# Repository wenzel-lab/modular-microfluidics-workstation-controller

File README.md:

# "Rio controller" the modular microfluidics controller 

This repository contains the free and *open-source* design and documentation for the *brain of a microfluidics workstation* to enable *high-throughput droplet microfluidic* biological assays. The design contains an electronics board "hat" that plugs onto a Raspberry Pi single-board computer and interfaces with our *compact* *modules* e.g. for gas-pressure control to push microfluidic samples onto chips, pressure, and flow measurement with feedback control, sample holders with heating and stirring, and imaging of fast droplet generation processes with open-source microscopy and stroboscopic illumination

Our aim is to create a prototype of a *compact* working station that is based on *connectable*, *open*, modern, and *low-cost* components (Rasberry Pi, Arduino, 3D printing, on-board components, open or at least accessible design software and operation software - python). This workstation is aimed to be fully functional research-grade equipment with good specifications, such as fast reaction times and low-pressure fluctuations. It is modular so that parts of the workstation can be repurposed and improved in the open-source hardware sense and easily combined, exchanged, or used independently in challenging environments such as an anaerobic chamber.

This is an open, collaborative project by the Wenzel Lab in Chile, and *your participation* (comments, inputs, contributions) are explicitly welcome! Please submit your message as an issue in this repository to participate.

> **Please Note:** This technical index is very much under construction and is at present an incomplete summary of the various documents that exist elsewhere in the Open Microfluidics Workstation repositories on GitHub and elsewhere.

Follow us! [#twitter](https://twitter.com/WenzelLab), [#YouTube](https://www.youtube.com/@librehub), [#LinkedIn](https://www.linkedin.com/company/92802424), [#instagram](https://www.instagram.com/wenzellab/), [#Printables](https://www.printables.com/@WenzelLab), [#LIBREhub website](https://librehub.github.io), [#IIBM website](https://ingenieriabiologicaymedica.uc.cl/en/people/faculty/821-tobias-wenzel)

<!--- ## Table of Contents --->

<!--- ## Background --->

## Usage

* Installation instructions
    * [Software installation](https://github.com/wenzel-lab/moldular-microfluidics-workstation-controller/wiki/Install-the-Software)
* Our modules are used in our [flow-microscopy-platform, see repostiory for documentation and instructions](https://github.com/wenzel-lab/flow-microscopy-platform)
* And it also powers our [strobe-enhanced microscopy stage](https://wenzel-lab.github.io/strobe-enhanced-microscopy-stage/) see also [it's repository](https://github.com/wenzel-lab/strobe-enhanced-microscopy-stage) 

## Design files and source code

* Hardware designs
    * [Fast imaging module](https://github.com/wenzel-lab/moldular-microfluidics-workstation-controller/tree/master/module-fast-imaging)
    * [Pressure and flow controller module](https://github.com/wenzel-lab/moldular-microfluidics-workstation-controller/tree/master/module-pressure-and-flow-controller)
    * [Sample holders module](https://github.com/wenzel-lab/moldular-microfluidics-workstation-controller/tree/master/module-sample-holders)
 
* Software source code
    * [Microfluidics workstation server](https://github.com/wenzel-lab/moldular-microfluidics-workstation-controller/blob/master/module-pi/webapp.zip) (This code runs on the built-in Raspberry Pi and includes the web application for the user interface.

### Modules Wish List
* High-pressure source module to replace large gas bottles with a small soda CO2 bottle, developed in this [sub-repository](https://github.com/wenzel-lab/moldular-microfluidics-workstation-controller/tree/master/module-high-pressure-source)
* Support for small piezo pumps
* Smart cultivation sleeves for vials, smaller and with OD-tracking - the V2 of our current sample holders and strirrers
* Microfluidic droplet sorting workstation driven by the droplet workstation tools is described [here](https://github.com/wenzel-lab/droplet-sorter-master/tree/main) (This is being developed in a separate repository).
  
## Contribute

Feel free to dive in! [Open an issue](https://github.com/wenzel-lab/moldular-microfluidics-workstation-controller/issues/new).
For interactions in our team and with the community applies the [GOSH Code of Conduct](https://openhardware.science/gosh-2017/gosh-code-of-conduct/).

## License

[CERN OHL 2W](LICENSE) © Tobias Wenzel, Christie Nel, and Pierre Padilla-Huamantinco. This project is Open-Source Hardware - please acknowledge us when using the hardware or sharing modifications.

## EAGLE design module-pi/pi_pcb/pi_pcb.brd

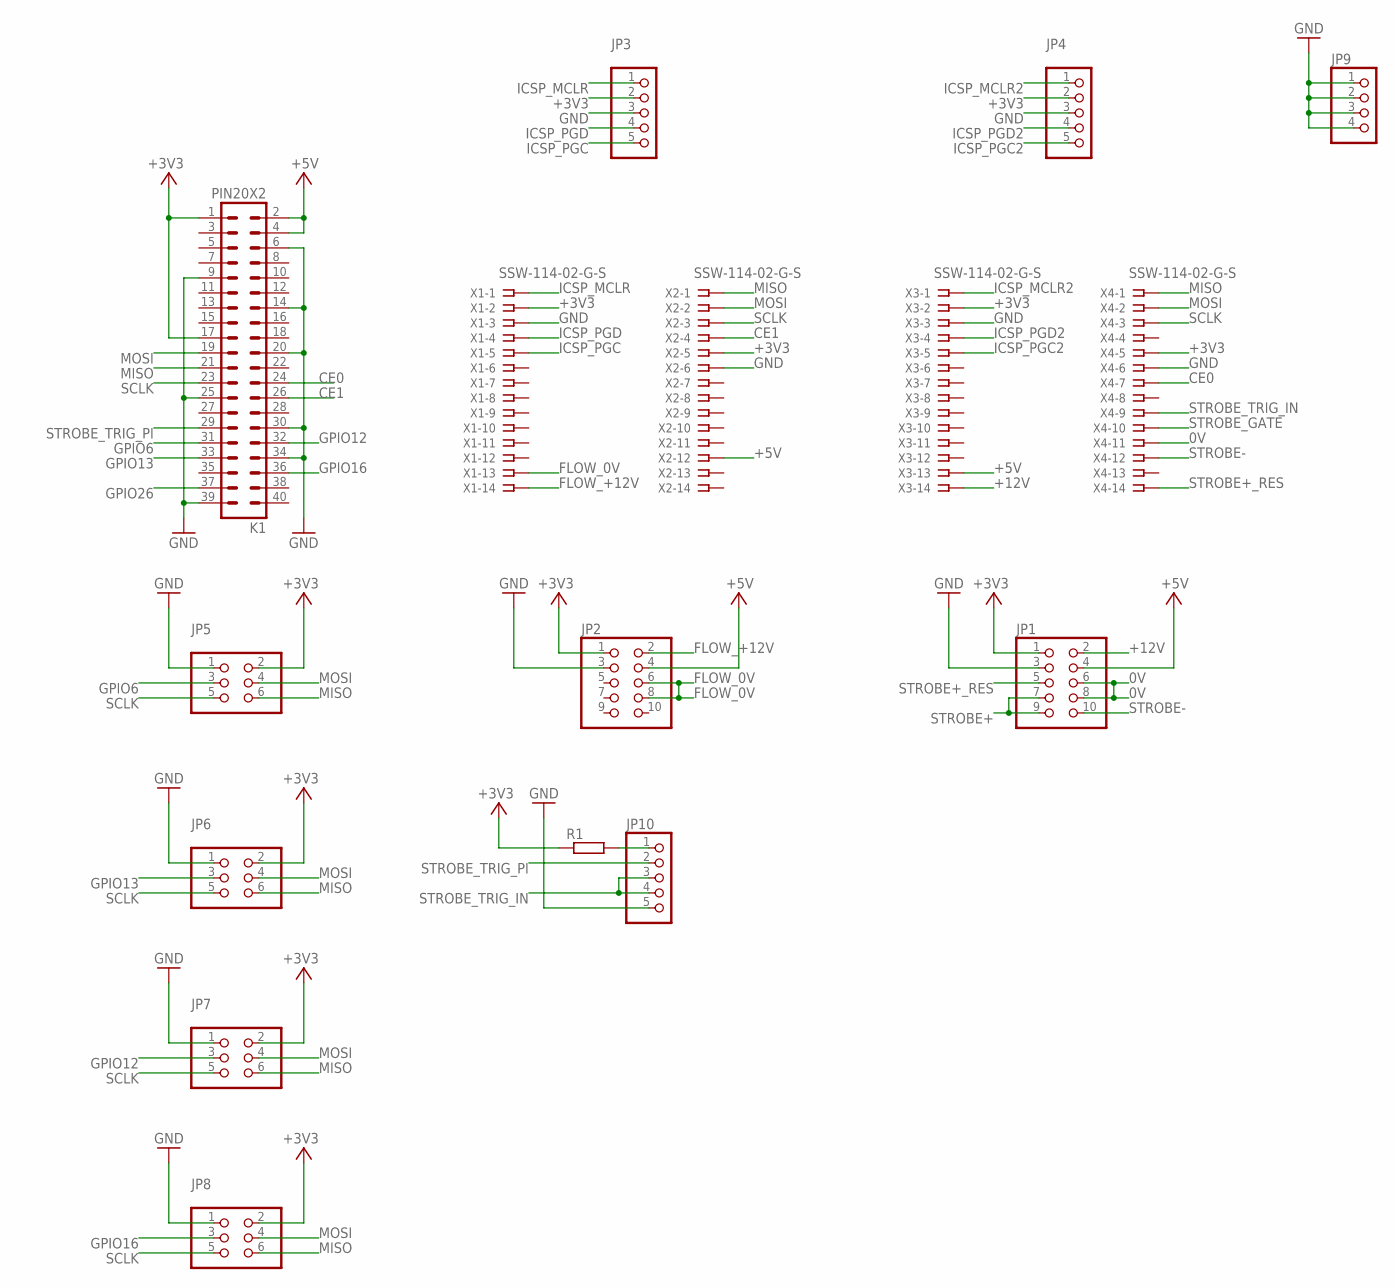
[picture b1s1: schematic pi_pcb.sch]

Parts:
JP1, JP2: PINHD-2X5; 2X05
JP3, JP4, JP10: PINHD-1X5; 1X05
JP5, JP6, JP7, JP8: PINHD-2X3; 2X03
JP9: PINHD-1X4; 1X04
K1: PIN20X2; PIN_20X2
R1: R-EU_R1206; R1206
X1, X2, X3, X4: SSW-114-02-G-S

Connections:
0V: JP1.6, JP1.8, X4.11
+3V3: JP1.1, JP2.1, JP3.2, JP4.2, JP5.2, JP6.2, JP7.2, JP8.2, K1.1, K1.17, R1.1, X1.2, X2.5, X3.2, X4.5
+5V: JP1.4, JP2.4, K1.2, K1.4, X2.12, X3.13
+12V: JP1.2, X3.14
CE0: K1.24, X4.7
CE1: K1.26, X2.4
FLOW_0V: JP2.6, JP2.8, X1.13
FLOW_+12V: JP2.2, X1.14
GND: JP1.3, JP2.3, JP3.3, JP4.3, JP5.1, JP6.1, JP7.1, JP8.1, JP9.1, JP9.2, JP9.3, JP9.4, JP10.5, K1.6, K1.9, K1.14, K1.20, K1.25, K1.30, K1.34, K1.39, X1.3, X2.6, X3.3, X4.6
GPIO6: JP5.3, K1.31
GPIO12: JP7.3, K1.32
GPIO13: JP6.3, K1.33
GPIO16: JP8.3, K1.36
GPIO26: K1.37
ICSP_MCLR: JP3.1, X1.1
ICSP_MCLR2: JP4.1, X3.1
ICSP_PGC: JP3.5, X1.5
ICSP_PGC2: JP4.5, X3.5
ICSP_PGD: JP3.4, X1.4
ICSP_PGD2: JP4.4, X3.4
MISO: JP5.6, JP6.6, JP7.6, JP8.6, K1.21, X2.1, X4.1
MOSI: JP5.4, JP6.4, JP7.4, JP8.4, K1.19, X2.2, X4.2
unnamed: JP10.1, R1.2
SCLK: JP5.5, JP6.5, JP7.5, JP8.5, K1.23, X2.3, X4.3
STROBE+: JP1.7, JP1.9
STROBE+_RES: JP1.5, X4.14
STROBE-: JP1.10, X4.12
STROBE_GATE: X4.10
STROBE_TRIG_IN: JP10.3, JP10.4, X4.9
STROBE_TRIG_PI: JP10.2, K1.29

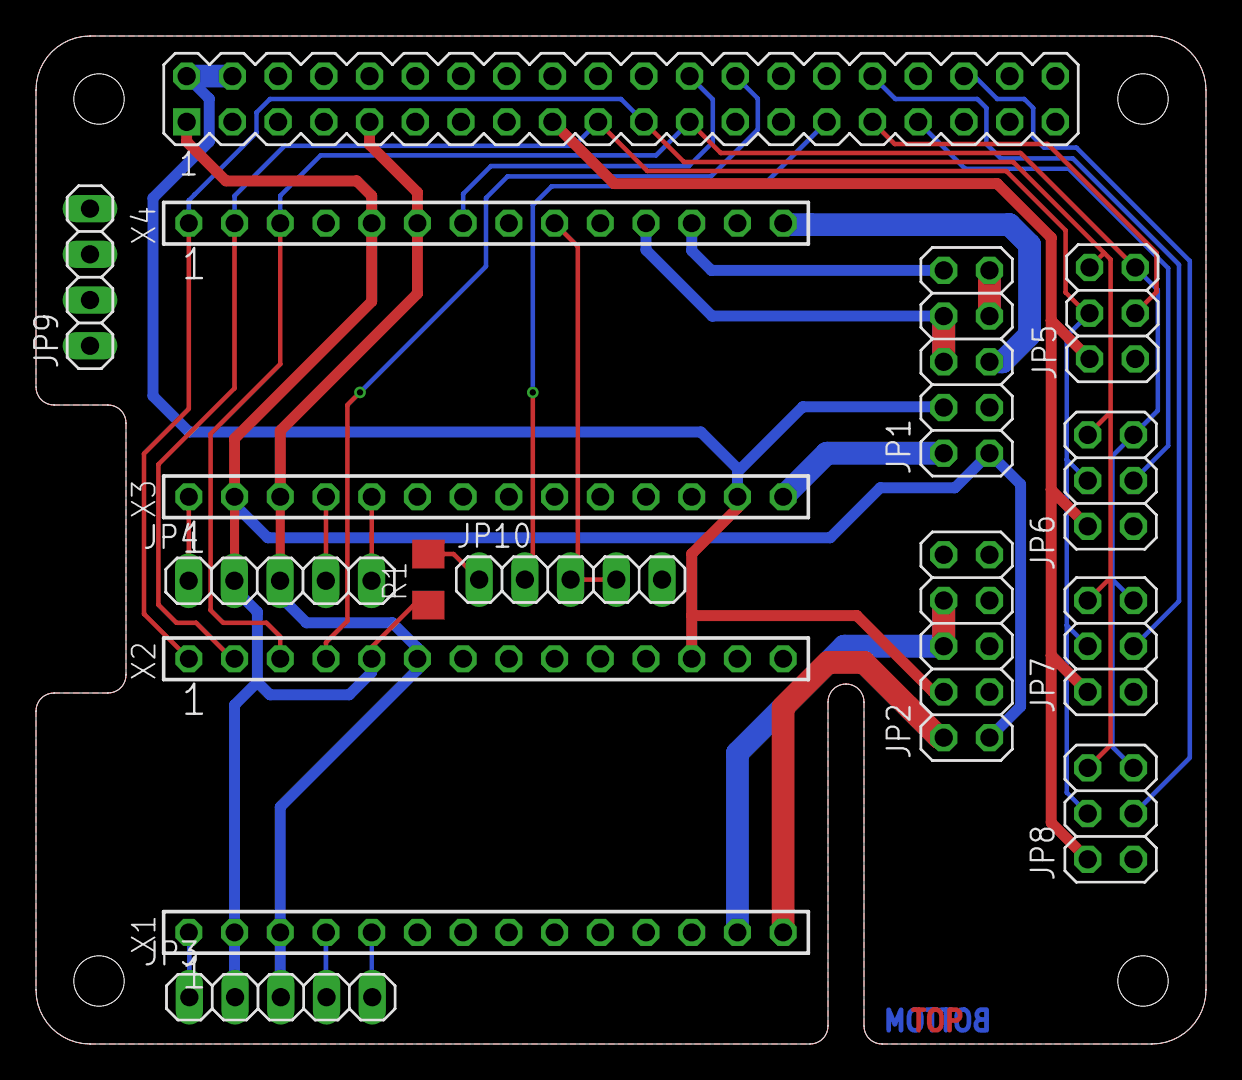
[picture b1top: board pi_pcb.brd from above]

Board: 2 copper layers, 65.0 x 56.0 mm, 16 parts (0 on the bottom side), 28 nets.

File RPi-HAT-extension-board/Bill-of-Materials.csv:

Item #,Ref Des,Full Name/Description,Category,Part/Catalog Number,Manufacturer/Supplier,Notes
,R1,RES SMD 1K OHM 1% 1/4W 1206,HAT,MCR18EZPF1001,Rohm Semiconductor,https://www.digikey.com/en/products/detail/rohm-semiconducto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
,"JP1, JP2","Header - 2x5 Pin (Male, 1.27mm)",HAT,PRT-15362,,https://www.sparkfun.com/header-2x5-pin-male-1-27mm.html
,"JP3, JP4, JP10",Header - 1x5 Pin,HAT,,,
,"JP5, JP6, JP7, JP8","Header - 2x3 (Male, 0.1"")",HAT,PRT-12807,,https://www.sparkfun.com/header-2x3-male-0-1.html
,JP9,Header - 1x4 Pin,HAT,,,
,K1,"Female Header: 2x20-Pin, Straight",HAT,,,https://www.pololu.com/product/1037
,"X1, X2, X3, X4","14-Contact, 1-Row, 2.54mm Pitch, Solder Termination",HAT,,,https://uk.rs-online.com/web/p/pcb-sockets/7655770

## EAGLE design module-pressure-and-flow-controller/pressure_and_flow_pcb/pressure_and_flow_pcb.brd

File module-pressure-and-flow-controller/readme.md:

## Pressure and flow controller module

This is the core piece of the workstation. 
This electronic controller module aims to regulate and distrbute the pressure (originating from the pressure source module) into the sample tubes, so that the samples (aqueous, gel pre-cursors and oils) flow onto the microfluidic chip and the collection reservoirs.
We aim to regulate pressures enough for ultra-high throughput agarose bead generation (several bar), in a smooth fashion that avoids pulsing, especially at steady state.
This controller consists of a custom circuit board that plugs into the Raspberry Pi hat, in addition to connectors for connecting external pressure controllers and flow sensors. Pressure and flow control are fully automatic.

The controller module can operate either in pressure control mode or flow control mode.  Flow control mode requires external flow sensors to be connected.  Once desired flow rates have been achieved and associated pressures are known, the experiment can be reproduced using only pressure control, without the need for expensive flow sensors.  Both modes require external pressure controllers to be connected.

The module contains a PIC microcontroller that communicates with the Raspberry Pi, controls the pressure controllers and reads back pressure and flow.  The pressure target is controlled using a digital-to-analogue converter and the actual pressure is read using an analogue-to-digital converter.  The flow controllers is read via a four channel I2C multiplexer.

### Pressure Controllers
We have selected the SMC ITV0010 pressure controllers for this application.  The pressure target is supplied to the pressure controller by the module as an analogue voltage and the measured pressure achieved is returned as an analogue voltage.  This approach allows the option to connect alternative analogue pressure controllers, or using a separate pressure sensor instead of the one internal to the pressure controller.

The ITV0010 pressure controllers can be purchased as a compact DIN-mounted manifold block that requires a single pressure supply line.

### Flow Sensors
We have selected the Sensirion LG16 range of flow sensor.  They feature a digital interface via I2C.

### Connectors

The module features eight Picoblade connectors.  Four connect to the pressure controllers, carrying power, analogue out and analogue in.  The other four connect to the optional flow sensors and carry power and I2C signals.  The module itself is designed to plug into the Raspberry Pi hat.  This allows for power and digital communications with the Raspberry Pi.

#### Pressure Controller Connector

|Pin|Description|
|-|-|
|1|Pressure In|
|2|Pressure Out|
|3|0V Power / GND|
|4|12V Power|

#### Flow Sensor Connector

|Pin|Description|
|-|-|
|1|I2C Data|
|2|Vdd 3.3V|
|3|Vss (Digital Ground)|
|4|I2C Clock|

**Note:** Pin 2 (Vdd 3.3V) must not be used to power Sensirion LG16 sensors, which require 5V.  This 3.3V pin was intended for use with the Sensirion SLF3S-1300F.  Instead use the 5V pin on the Controller Module header block on the Raspberry Pi hat.

### Pinout

|Pin|Description|
|-|-|
|1|ICSP MCLR|
|2|ICSP Vdd (3V3 Power)|
|3|ICSP Vss (Digital Ground)|
|4|ICSP Data|
|5|ICSP Clock|
|13|Ground for 12V|
|14|12V Supply for Pressure Controllers|
|17|5V Digital Power|
|23|Digital Ground|
|24|Digital 3.3V Power|
|25|SPI Slave Select|
|26|SPI Clock|
|27|SPI MOSI|
|28|SPI MISO|

**Note:** Pin 13 (12V Ground) must be connected with pin 23 (digital ground) externally, and in a way that prevents ground loops.

### PCB Components

|Qty|Name|Component|Description|
|-|-|-|-|
|7|C1-C5,C8-C9|100nf Capacitor 0603|Decoupling Capacitors|
|2|C6,C10|10uF Capacitor 0603|Bypass,Bulk Capacitor|
|1|C7|Not fitted||
|1|C2|dsPIC33CK256MP502-I/SS SSOP28|PIC Microprocessor|
|1|C3|AD5624R|DAC|
|1|C4|ADS1115|ADC|
|1|C5|PCA9544APW,112|I2C Multiplexer|
|1|C6|25AA040ST|EEPROM|
|12|R1-R10,R12-R13|1k Resistor 0603||
|1|R11|10k Resistor 0603||
|8|X1-X8|Picoblade 53047-0410|Connectors|

Please note that our current implementation is based on compact, low-cost and scalable PIC microcontrollers that fit onto the Pi-hat modules. These cannot simply be programmed with a micro-USB cables. Instead, they need an [additional small hardware ICSP interface](https://www.digikey.com/en/product-highlight/m/microchip-technology/pickit-3-in-circuit-debugger-programmer) (or equivalent) to load new code onto the PIC microcontrollers.

### Cable for Sensirion LG16

Flow Controller Module End

Connector Type: Picoblade 1.25mm 4-way (51021-0400)<br/>
Connector Crimps: Picoblade 26-28 AWG (50079-8000)

|Pin|Wire|Function|
|-|-|-|
|1|1|I2C Data|
|2|-|Not Connected|
|3|3|VSS|
|4|4|I2C Clock|

Connector Type: DuPont Standard Female

|Pin|Wire|Function|
|-|-|-|
|1|2|VDD 5V|

Flow Sensor End (Sensirion LG16)

Connector Type: Picoblade 1.25mm 5-way (51021-0500)<br/>
Connector Crimps: Picoblade 26-28 AWG (50079-8000)

|Pin|Wire|Function|
|-|-|-|
|1|1|I2C Data|
|2|4|I2C Clock|
|3|2|VDD 5V|
|4|3|VSS|
|5|-|Not Connected|

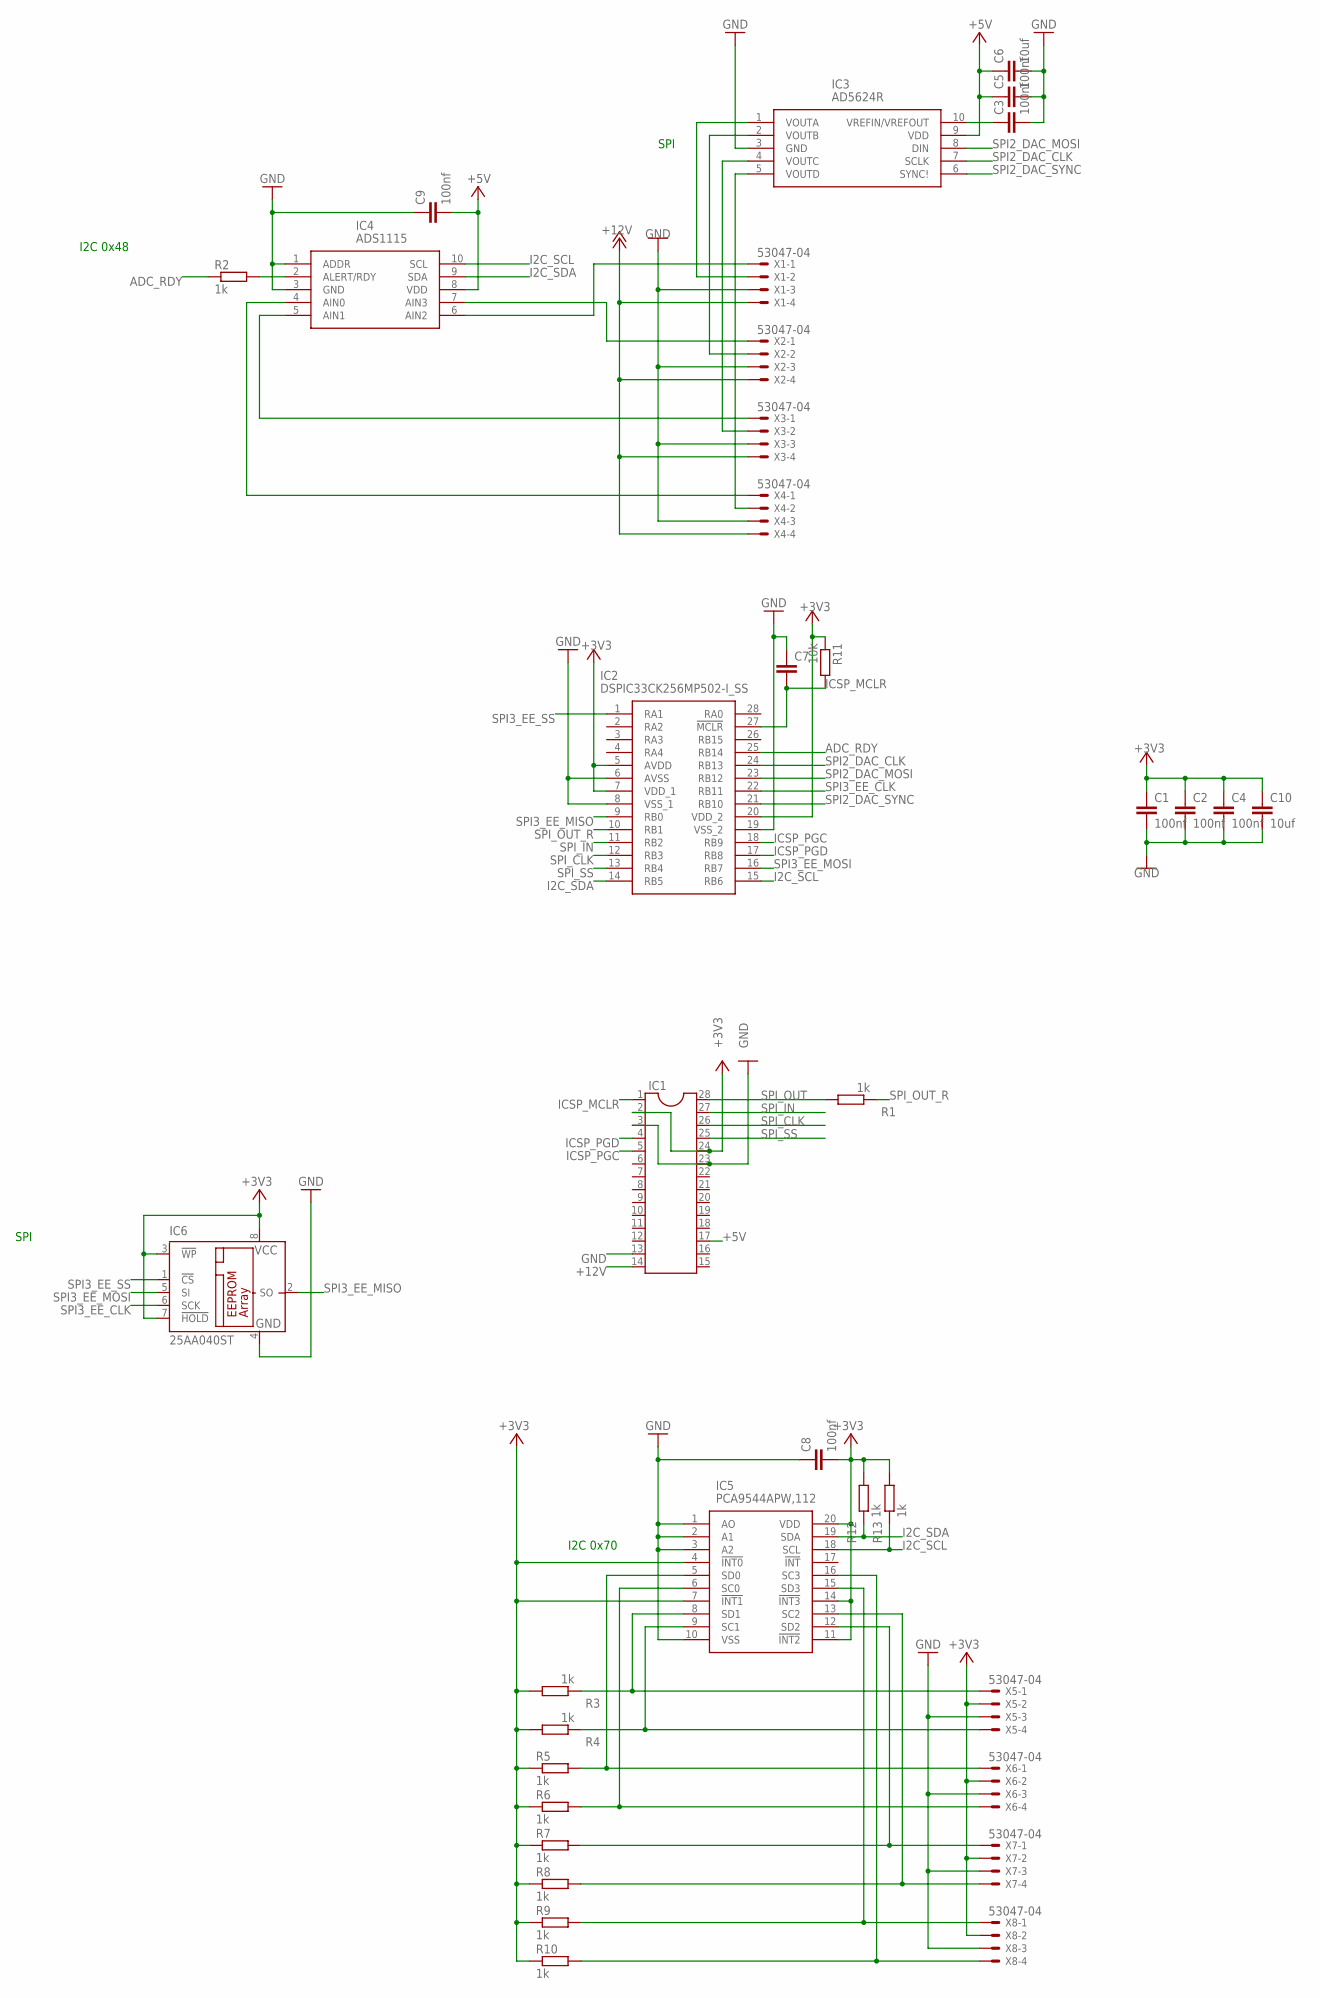
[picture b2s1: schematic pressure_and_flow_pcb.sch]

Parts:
C1, C2, C3, C4, C5, C8, C9: 100nf; C0603K
C6, C10: 10uf; C0603K
C7: C-EUC0603K; C0603K
IC1: DIL28; DIL28-6
IC2: DSPIC33CK256MP502-I_SS; SOP65P780X200-28N
IC3: AD5624R; SOP50P490X110-10N
IC4: ADS1115; SOP50P490X110-10N
IC5: PCA9544APW,112; SOP65P640X110-20N
IC6: 25AA040ST; TSSOP8
R1, R2, R3, R4, R5, R6, R7, R8, R9, R10, R12, R13: 1k; R0603
R11: 10k; R0603
X1, X2, X3, X4, X5, X6, X7, X8: 53047-04

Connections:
+3V3: C1.1, C2.1, C4.1, C8.2, C10.1, IC1.2, IC1.24, IC2.5 (AVDD), IC2.7 (VDD_1), IC2.20 (VDD_2), IC5.4 (!INT0), IC5.7 (!INT1), IC5.11 (!INT2), IC5.14 (!INT3), IC5.20 (VDD), IC6.3 (!WP), IC6.7 (!HOLD), IC6.8 (VCC), R3.2, R4.2, R5.1, R6.1, R7.1, R8.1, R9.1, R10.1, R11.1, R12.2, R13.2, X5.2, X6.2, X7.2, X8.2
+5V: C5.1, C6.1, C9.2, IC1.17, IC3.9 (VDD), IC4.8 (VDD)
+12V: IC1.14, X1.4, X2.4, X3.4, X4.4
ADC_RDY: IC2.25 (RB14), R2.1
GND: C1.2, C2.2, C3.2, C4.2, C5.2, C6.2, C7.1, C8.1, C9.1, C10.2, IC1.3, IC1.13, IC1.23, IC2.6 (AVSS), IC2.8 (VSS_1), IC2.19 (VSS_2), IC3.3 (GND), IC4.1 (ADDR), IC4.3 (GND), IC5.1 (AO), IC5.2 (A1), IC5.3 (A2), IC5.10 (VSS), IC6.4 (GND), X1.3, X2.3, X3.3, X4.3, X5.3, X6.3, X7.3, X8.3
I2C_SCL: IC2.15 (RB6), IC4.10 (SCL), IC5.18 (SCL), R13.1
I2C_SDA: IC2.14 (RB5), IC4.9 (SDA), IC5.19 (SDA), R12.1
ICSP_MCLR: C7.2, IC1.1, IC2.27 (!MCLR), R11.2
ICSP_PGC: IC1.5, IC2.18 (RB9)
ICSP_PGD: IC1.4, IC2.17 (RB8)
unnamed: C3.1, IC3.10 (VREFIN/VREFOUT)
unnamed: IC3.1 (VOUTA), X1.2
unnamed: IC3.2 (VOUTB), X2.2
unnamed: IC3.4 (VOUTC), X3.2
unnamed: IC4.2 (ALERT/RDY), R2.2
unnamed: IC4.5 (AIN1), X3.1
unnamed: IC3.5 (VOUTD), X4.2
unnamed: IC5.5 (SD0), R5.2, X6.1
unnamed: IC5.6 (SC0), R6.2, X6.4
unnamed: IC5.8 (SD1), R3.1, X5.1
unnamed: IC5.9 (SC1), R4.1, X5.4
unnamed: IC5.12 (SD2), R7.2, X7.1
unnamed: IC5.13 (SC2), R8.2, X7.4
unnamed: IC5.15 (SD3), R9.2, X8.1
unnamed: IC5.16 (SC3), R10.2, X8.4
unnamed: IC4.7 (AIN3), X2.1
unnamed: IC4.6 (AIN2), X1.1
unnamed: IC4.4 (AIN0), X4.1
SPI2_DAC_CLK: IC2.24 (RB13), IC3.7 (SCLK)
SPI2_DAC_MOSI: IC2.23 (RB12), IC3.8 (DIN)
SPI2_DAC_SYNC: IC2.21 (RB10), IC3.6 (SYNC!)
SPI3_EE_CLK: IC2.22 (RB11), IC6.6 (SCK)
SPI3_EE_MISO: IC2.9 (RB0), IC6.2 (SO)
SPI3_EE_MOSI: IC2.16 (RB7), IC6.5 (SI)
SPI3_EE_SS: IC2.1 (RA1), IC6.1 (!CS)
SPI_CLK: IC1.26, IC2.12 (RB3)
SPI_IN: IC1.27, IC2.11 (RB2)
SPI_OUT: IC1.28, R1.2
SPI_OUT_R: IC2.10 (RB1), R1.1
SPI_SS: IC1.25, IC2.13 (RB4)

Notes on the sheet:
I2C 0x48
SPI
I2C 0x70

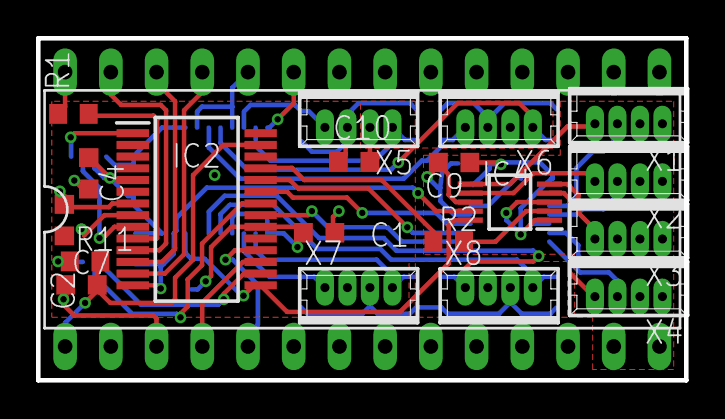
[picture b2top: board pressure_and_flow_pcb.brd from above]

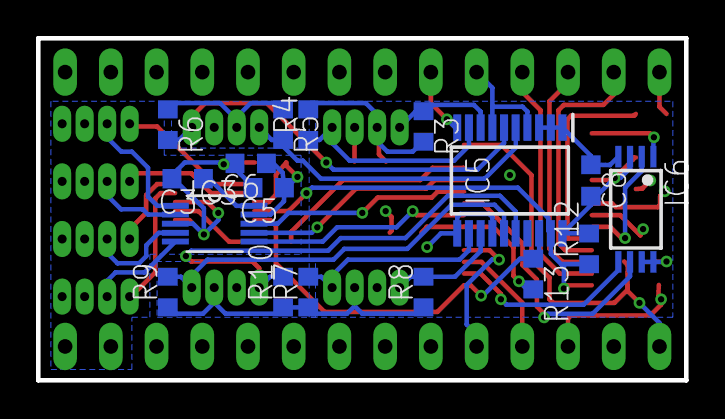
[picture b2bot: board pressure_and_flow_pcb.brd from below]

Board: 4 copper layers, 36.0 x 19.0 mm, 37 parts (17 on the bottom side), 40 nets.

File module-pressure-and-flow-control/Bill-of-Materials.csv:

Item #,Ref Des,Full Name/Description,Category,Part/Catalog Number,Manufacturer/Supplier,Notes
7,C1-C5;C8-C9,100nf Capacitor 0603,,,,Decoupling Capacitors
2,C6;C10,10uF Capacitor 0603,,,,Bypass / Bulk Capacitor
1,C7,Not fitted,,,,
1,IC2,PIC Microprocessor,,dsPIC33CK256MP502-I/SS SSOP28,,
1,IC3,DAC,,AD5624R,,
1,IC4,ADC,,ADS1115,,
1,IC5,I2C Multiplexer,,PCA9544APW;112,,
1,IC6,EEPROM,,25AA040ST,,
12,R1-R10;R12-R13,1k Resistor 0603,,,,
1,R11,10k Resistor 0603,,,,
8,X1-X8,Connectors,,Picoblade 53047-0410,,

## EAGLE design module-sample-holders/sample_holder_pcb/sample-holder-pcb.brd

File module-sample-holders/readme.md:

# Sample Holder Module

The sample holder is used to heat microfluidic sample liquids such as water, oil or agarose to a set temperature and optionally stirring the sample using a magnetic stir bar, before pumping it through a microfluidics chip.  The PCB can also be used separately with external heaters to heat tubing or microscope glass slides.

The sample holder module comprises a PCB, two cartridge heaters, temperature sensor and stirring motor and magnets, all integrated into an aluminium shell.  Aluminium inserts that slot into the top can be machined to accommodate sample bottles of various shapes and sizes.  The sample holder connects to a Raspberry Pi via SPI, from which the sample holder temperature and stir speed are set and monitored.

The sample holder has been tested to 100 degrees Celcius and provides a stable (but uncalibrated) readout to 0.01 degrees Celcius.

## PCB

The sample holder PCB is the heart of the sample holder and contains a PIC microprocessor that reads the temperature sensor, controls the heaters and stirrer motor and offers an SPI interface to a host.

The PCB has been designed for dual use.  It can be mounted in a sample holder with heaters, temperature sensor and stir motor wires soldered to the PCB.  Alternatively, it can also be used with external heater and temperature sensor attached via the secondary connector as shown below.

The connector on the left is the primary connector and provides 12V power for the heaters, 3.3V power for the microprocessor and SPI communications with the Raspberry Pi.

The connector on the right is the secondary connector that connects to the external heater (black wires) and temperature sensor (white wires).  The polarity of heater and temperature sensor does not matter.  The connector also provides debug serial output and ICSP interface for reprogramming the PIC microprocessor.

### PCB Primary Connector : Power and SPI Interface

|Pin|Description|
|-|-|
|1|SPI Clock|
|2|SPI Slave Select|
|3|Vdd 3.3V|
|4|SPI MOSI|
|5|Vss (Digital Ground)|
|6|SPI MISO|
|7|Heater 0V|
|8|Heater 12V|
|9|Heater 0V|
|10|Heater 12V|

**Note:** Vss(GND) must be connected with Heater 0V, and in a way that prevents ground loops.

### PCB Secondary Connector : External Heater, Temperature Sensor, Debug Serial and Programming Interface (ICSP)

|Pin|Description|
|-|-|
|1|Heater Out 12V|
|2|ICSP MCLR|
|3|Heater Out 0V|
|4|ICSP 3.3V|
|5|Temp Sensor (Vss)|
|6|ICSP GND (Vss)|
|7|Temp Sensor +|
|8|ICSP PGD|
|9|Serial Debug TX|
|10|ICSP PGC|

**Note:** Do not supply ICSP 3.3V while also supplying Vdd 3.3V as they are connected.

### PCB FET Mounting

A power FET is mounted on the bottom of the PCB and drives the heaters.  It is intended to touch the metal the PCB is mounted on, with thermal paste between FET and metal.

### PCB Components

|Qty|Name|Component|Description|
|-|-|-|-|
|1|IC2|dsPIC33CK256MP502-I/SS SSOP28|PIC Microprocessor|
|1|IC1|25AA128-I/ST TSSOP8|SPI EEPROM|
|1|Q1|AUIRFU8403 IPAK|MOSFET|
|2|T1,T3|MMBT3904LT1 SOT23|NPN Transistor|
|2|T2,T4|MMBT3906LT1 SOT23|PNP Transistor|
|1|LED1|LTST-S270KGKT 0603|Green Side View LED|
|2|J1,J2|10 Pin 2 Row Angled Header||
|1|R7|3.3k Resistor|Temperature Sensor Reference|
|6|R1-R6|1k Resistor 0603||
|1|R9|10k Resistor 0603|PIC MCLR Pull Up|
|1|R8|120R Resistor 0603|LED Resistor|
|4|C1,C2,C4,C6|100nf Capacitor 0603|Decoupling Capacitors|
|1|C3|1nf Capacitor 0603|Motor Drive Capacitor|
|1|C5|10uf Capacitor 1206|Bulk Capacitor|

## Heaters and Sensors

The heaters are 3.3 Ohm (rated 12V, 40W) stainless steel cartridges that insert into holes drilled into the top section of the sample holder.  A temperature sensor is inserted into a hole drilled into the same section.  The temperature sensor is a negative coefficient thermister (NTC).  These heaters and temperature sensors are commonly used in 3D printers and can be found on eBay or Amazon.

## Stirrer Motor and Magnets

The stirrer motor rotates two attached magnets, which in turn rotate an optional stirrer magnet in the sample bottle inserted into the top of the sample holder.

The stirrer motor is a standard 40mm x 40mm x 10mm, three wire fan.  The rotating side points upward and has two 6mm diameter x 2mm thick Neodymium magnets mounted flat next to each other (opposing poles same side) in the centre of the fan.  The magnets have to be raised off the fan such that their fields do not interfere with the operation of the fan, be close enough to the stirrer magnet, while not touching the opposing surface.  We find that raising it 3-4mm with layers of double sided tape is sufficient and provides enough strength to spin the stirrer magnet.  The fan wire colours are typically black=ground, red=12V, yellow=sense/tachometer.

## Power Considerations

The heaters can draw quite a lot of power, so an adequate 12V power supply must be provided.  At full power with two 3.3 Ohm heaters, the required current can be calculated as:
I = ( 12V / 3.3 Ohm ) * 2 heaters = 7.3A
The maximum power can be limited by storing a power limit percentage to the sample holder via SPI.  Alternatively, these 40W heater cartridges are also made for 24V, which have around 4x the resistance (P=V^2/R, 40=24^2/R, R=14.4 Ohm) and will thus consume 1/4 as much power, but heat more slowly.

## Mechanical Design

The sample holder is constructed from layers of machined 54mm diameter aluminium rod as listed in the table below.  The overall dimensions and screw locations are determined by the 40mm fan used as a stir motor.

|Section|Description|
|---|---|
|Top|The top section houses the two heater cartridges and temperature sensor and is the part that gets hot.  It also houses an insert that is shaped to fit a particular sample vessel.|
|Insulation|A layer of FR4 material that insulates the heated top from the rest of the module.|
|Magnet Space|A cavity above the motor/fan where the stir magnets rotate.|
|Motor|The stir motor that rotates the stir magnets.|
|PCB Mount|The plate that the PCB is mounted on with standoffs.  This plate also used as a heatsink for the FET that protrudes from the PCB.|
|PCB Spacer|The cavity for the PCB and wires.|
|Bottom|The bottom plate that closes up the PCB cavity and also holds the screw heads.|

[Download Mechanical Design PDF](doc/sample_holder_design.pdf)

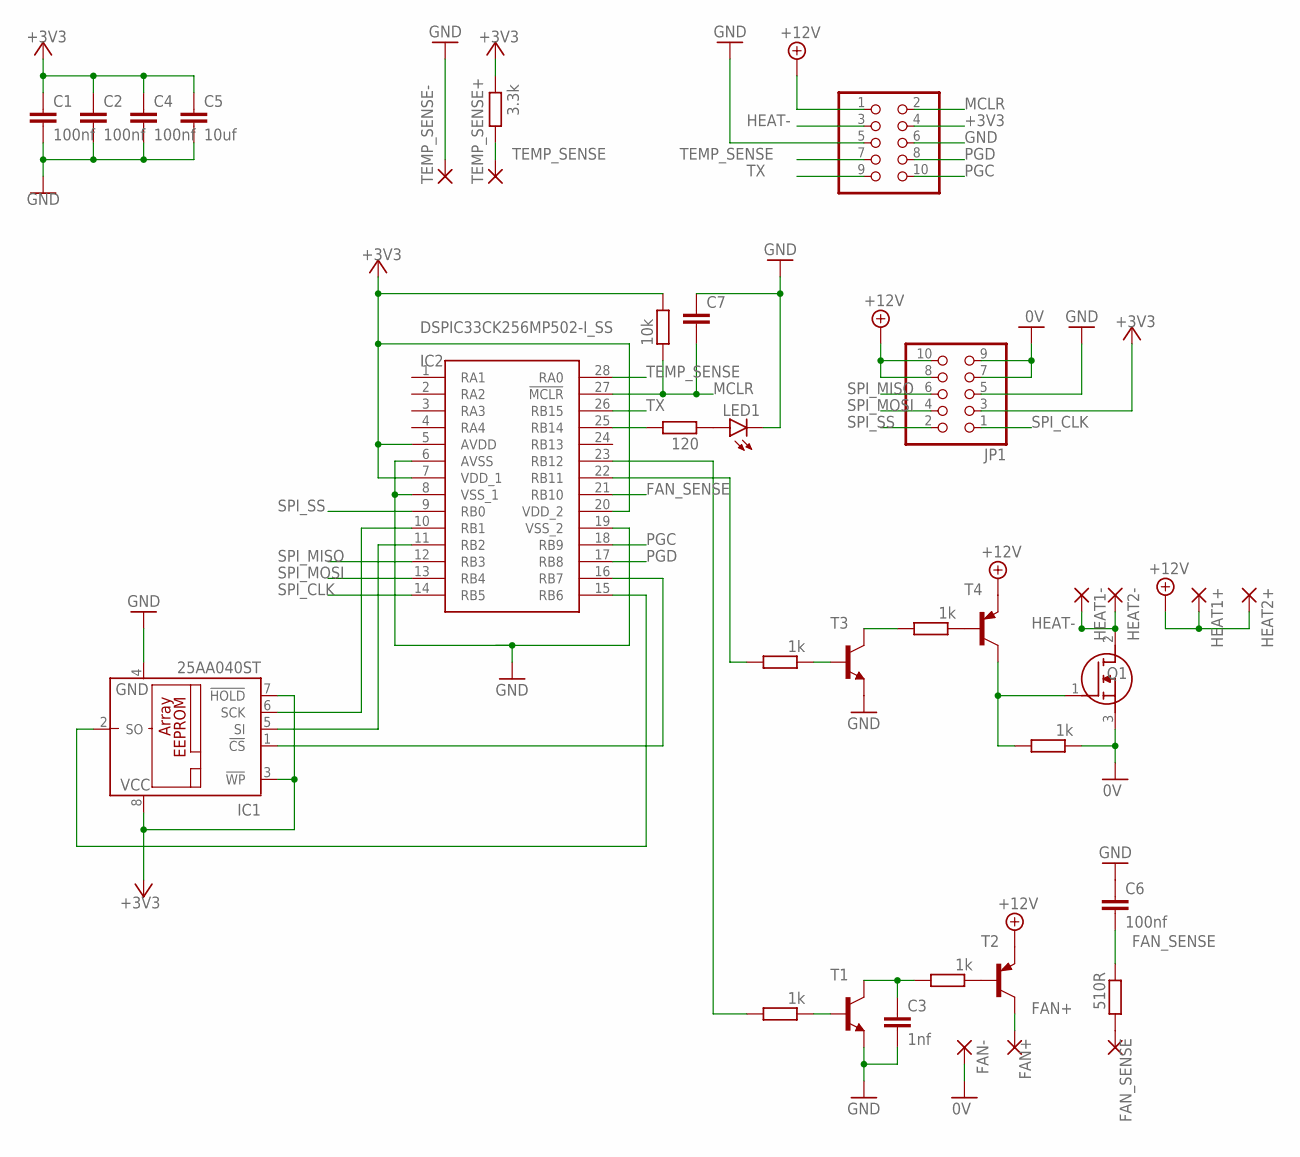
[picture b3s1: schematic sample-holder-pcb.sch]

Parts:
C1, C2, C4, C6: 100nf; C0603
C3: 1nf; C0603
C5: 10uf; C1206
C7: C-EUC0603; C0603
FAN+: 1,6/0,8
FAN-: 1,6/0,8
FAN_SENSE: 1,6/0,8
HEAT1+, HEAT1-, HEAT2+, HEAT2-: 2,54/1,0
IC1: 25AA040ST; TSSOP8
IC2: DSPIC33CK256MP502-I_SS; SOP65P780X200-28N
JP1, JP2: PINHD-2X5/90; 2X05/90
LED1: LEDSML0603; SML0603
Q1: AUIRFU8403; TO229P239X654X978-3P
R1, R2, R3, R4, R5: 1k; R0603
R6: 510R; R0603
R7: 3.3k; R0603
R8: 120; R0603
R9: 10k; R0603
T1, T3: MMBT3904LT1-NPN-SOT23-BEC; SOT23-BEC
T2, T4: MMBT3906LT1-PNP-SOT23-BEC; SOT23-BEC
TEMP_SENSE+: 1,6/0,8
TEMP_SENSE-: 1,6/0,8

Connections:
0V: FAN-.1, JP1.7, JP1.9, Q1.3 (S), R5.1
+3V3: C1.1, C2.1, C4.1, C5.1, IC1.3 (!WP), IC1.7 (!HOLD), IC1.8 (VCC), IC2.5 (AVDD), IC2.7 (VDD_1), IC2.20 (VDD_2), JP1.3, JP2.4, R7.1, R9.1
+12V: HEAT1+.1, HEAT2+.1, JP1.8, JP1.10, JP2.1, T2.E, T4.E
FAN+: FAN+.1, T2.C
FAN_SENSE: C6.2, IC2.21 (RB10), R6.1
GND: C1.2, C2.2, C3.2, C4.2, C5.2, C6.1, C7.1, IC1.4 (GND), IC2.6 (AVSS), IC2.8 (VSS_1), IC2.19 (VSS_2), JP1.5, JP2.5, JP2.6, LED1.C, T1.E, T3.E, TEMP_SENSE-.1
HEAT-: HEAT1-.1, HEAT2-.1, JP2.3, Q1.2 (D)
MCLR: C7.2, IC2.27 (!MCLR), JP2.2, R9.2
unnamed: R2.1, T3.B
unnamed: R4.2, T3.C
unnamed: R4.1, T4.B
unnamed: Q1.1 (G), R5.2, T4.C
unnamed: FAN_SENSE.1, R6.2
unnamed: LED1.A, R8.2
unnamed: IC2.25 (RB14), R8.1
unnamed: R1.1, T1.B
unnamed: C3.1, R3.2, T1.C
unnamed: R3.1, T2.B
unnamed: IC2.22 (RB11), R2.2
unnamed: IC1.5 (SI), IC2.11 (RB2)
unnamed: IC1.6 (SCK), IC2.10 (RB1)
unnamed: IC1.2 (SO), IC2.15 (RB6)
unnamed: IC1.1 (!CS), IC2.16 (RB7)
unnamed: IC2.23 (RB12), R1.2
PGC: IC2.18 (RB9), JP2.10
PGD: IC2.17 (RB8), JP2.8
SPI_CLK: IC2.14 (RB5), JP1.1
SPI_MISO: IC2.12 (RB3), JP1.6
SPI_MOSI: IC2.13 (RB4), JP1.4
SPI_SS: IC2.9 (RB0), JP1.2
TEMP_SENSE: IC2.28 (RA0), JP2.7, R7.2, TEMP_SENSE+.1
TX: IC2.26 (RB15), JP2.9

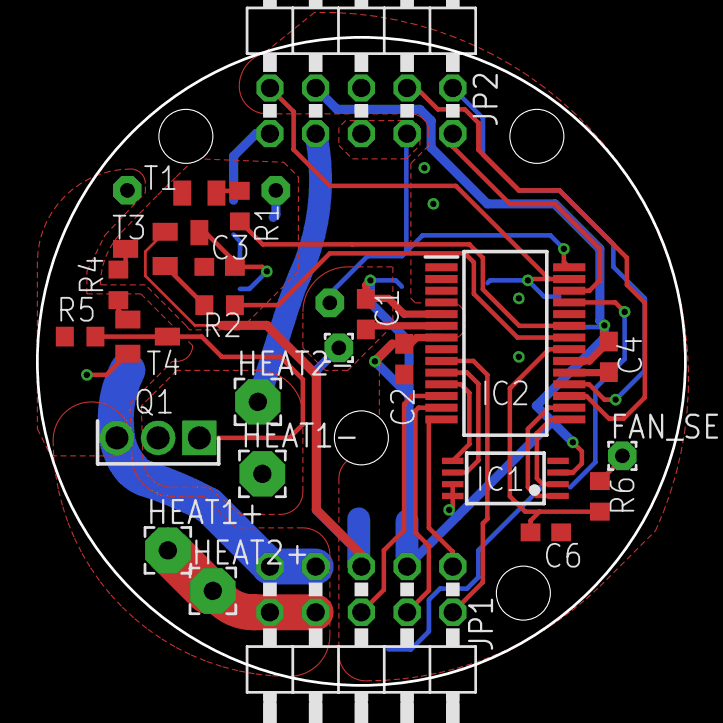
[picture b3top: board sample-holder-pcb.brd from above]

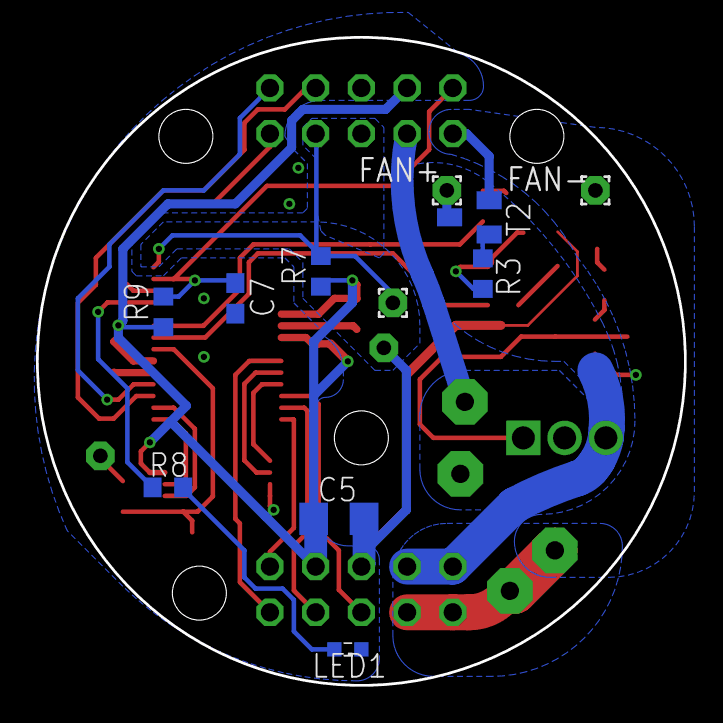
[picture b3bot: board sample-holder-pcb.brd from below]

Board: 2 copper layers, 36.0 x 36.0 mm, 35 parts (11 on the bottom side), 32 nets.

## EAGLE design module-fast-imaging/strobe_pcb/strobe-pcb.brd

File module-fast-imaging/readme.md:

## Fast imaging module for microfluidic droplet generation

Imaging unit based on compact 3D printed microscope (https://gitlab.com/openflexure/openflexure-microscope), with Objective (10x?)

Depending on the load demand, it could operate on the Raspberri Pi computer of the central workstation unit, have it's own computer, and transfer images to a webserver

All versions aim for a userfriendly / self-tuning controll of a stroboscopic illumination (simple high-power LED controlled by Arduino style microcontroller, in turn controlled by the Raspberri Pi where images are processed / viewed and saved/ sent to server)

### Approach Nr.1 Integrated camera

Low-cost integrated use of Raspberri Pi Camera V2 and scripting to vary image size vs. frame rate.

Instruction examples:

https://hackaday.com/2019/08/10/660-fps-raspberry-pi-video-captures-the-moment-in-extreme-slo-mo/

https://gist.github.com/CarlosGS/b8462a8a1cb69f55d8356cbb0f3a4d63#gistcomment-2108157

https://blog.robertelder.org/recording-660-fps-on-raspberry-pi-camera/

https://github.com/Hermann-SW/Raspberry_v1_camera_global_external_shutter

### Approach Nr.2 USB3 camera

Use of high-speed camera and USB3 connection on the Raspberri Pi 4

E.g. Compact cameras from Allied Vision 

Camera Mako U-051B mono; 800x600 CMOS C-Mount 391fps 10bit-ADC 128MB-buffer; ca. 340 Euro net

Camera Mako U-029B mono; 640x480 CMOS C-Mount 550fps 10bit-ADC 128MB-buffer; ca. 300 Euro net

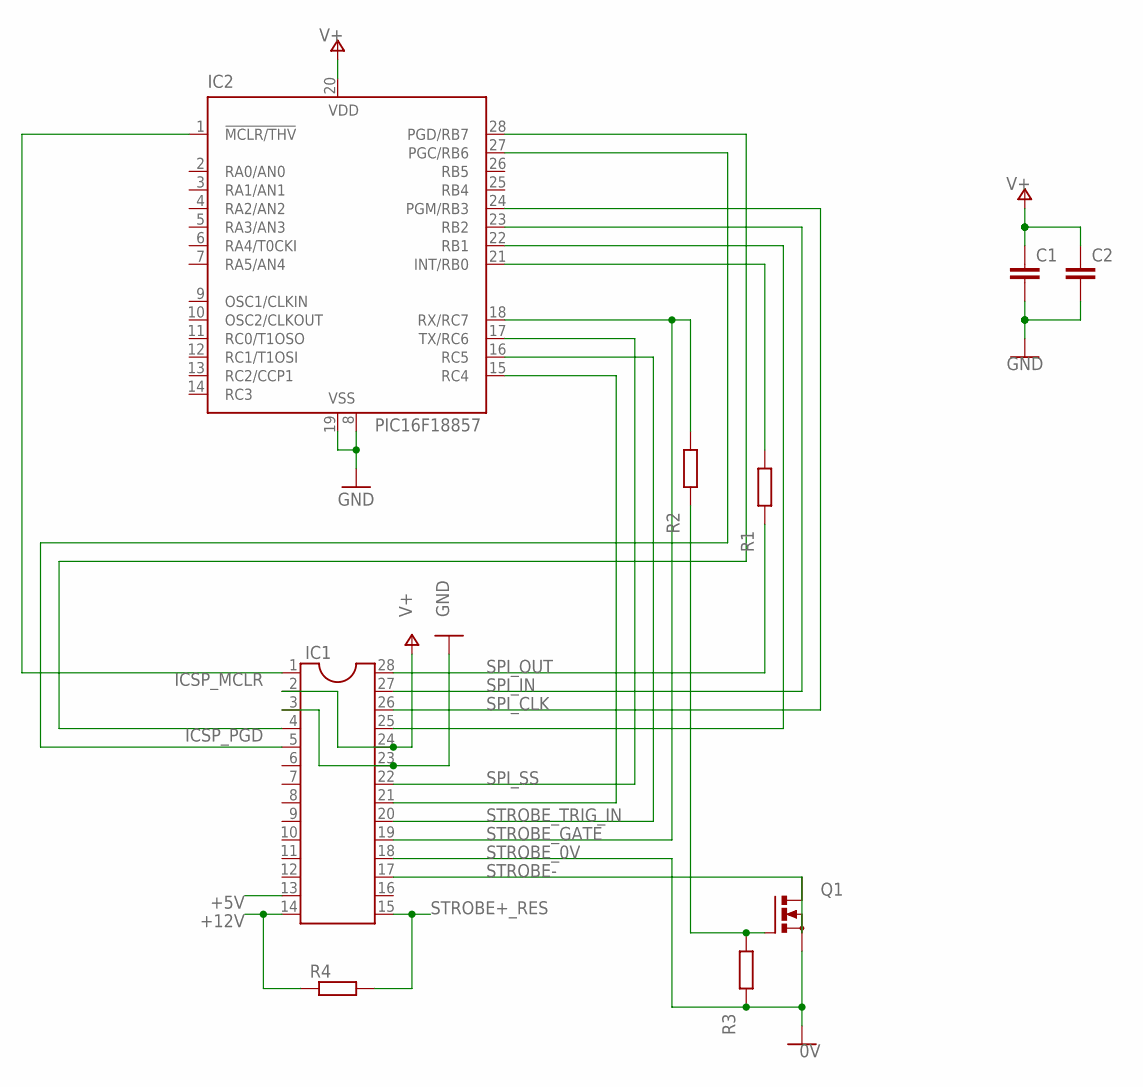
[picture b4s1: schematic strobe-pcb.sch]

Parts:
C1, C2: C-EUC1206; C1206
IC1: DIL28; DIL28-6
IC2: PIC16F18857; SO28W
Q1: PMOSFET_NTO220BV; TO220BV
R1, R2, R3: R-EU_R1206; R1206
R4: R-EU_0207/10; 0207/10

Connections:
+5V: IC1.13
+12V: IC1.14, R4.1
GND: C1.2, C2.2, IC1.3, IC1.23, IC2.8 (VSS), IC2.19 (VSS)
ICSP_MCLR: IC1.1, IC2.1 (!MCLR/THV)
ICSP_PGD: IC1.4, IC2.28 (PGD/RB7)
unnamed: IC1.25, IC2.22 (RB1)
unnamed: IC2.21 (INT/RB0), R1.2
unnamed: IC1.5, IC2.27 (PGC/RB6)
unnamed: Q1.G, R2.1, R3.2
unnamed: IC1.21, IC2.15 (RC4)
SPI_CLK: IC1.26, IC2.24 (PGM/RB3)
SPI_IN: IC1.27, IC2.23 (RB2)
SPI_OUT: IC1.28, R1.1
SPI_SS: IC1.22, IC2.17 (TX/RC6)
STROBE+_RES: IC1.15, R4.2
STROBE-: IC1.17, Q1.D
STROBE_0V: IC1.18, Q1.S, R3.1
STROBE_GATE: IC1.19, IC2.18 (RX/RC7), R2.2
STROBE_TRIG_IN: IC1.20, IC2.16 (RC5)
V+: C1.1, C2.1, IC1.2, IC1.24, IC2.20 (VDD)

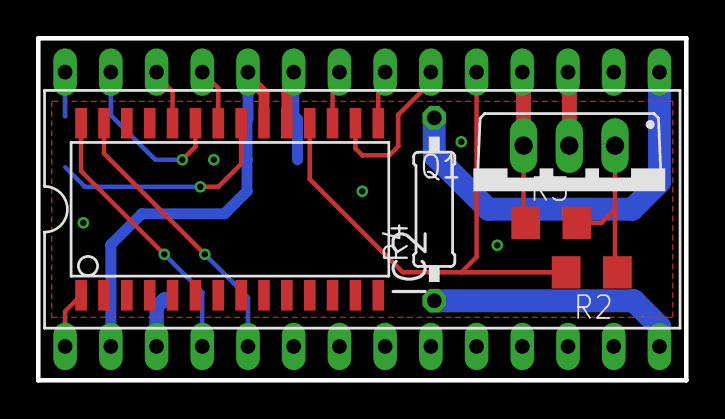
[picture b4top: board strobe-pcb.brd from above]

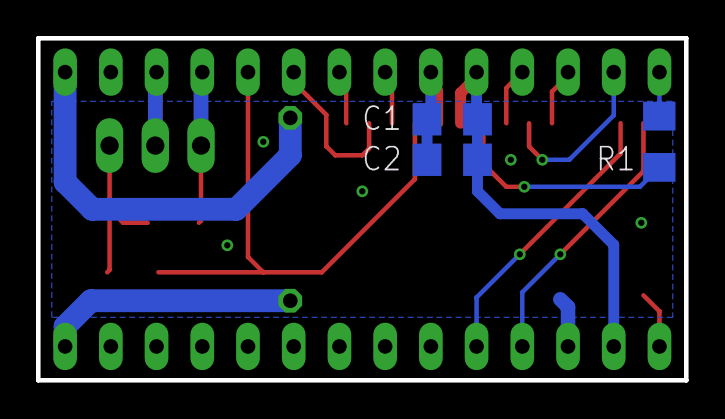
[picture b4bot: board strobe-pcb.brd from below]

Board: 2 copper layers, 36.0 x 19.0 mm, 9 parts (3 on the bottom side), 19 nets.
